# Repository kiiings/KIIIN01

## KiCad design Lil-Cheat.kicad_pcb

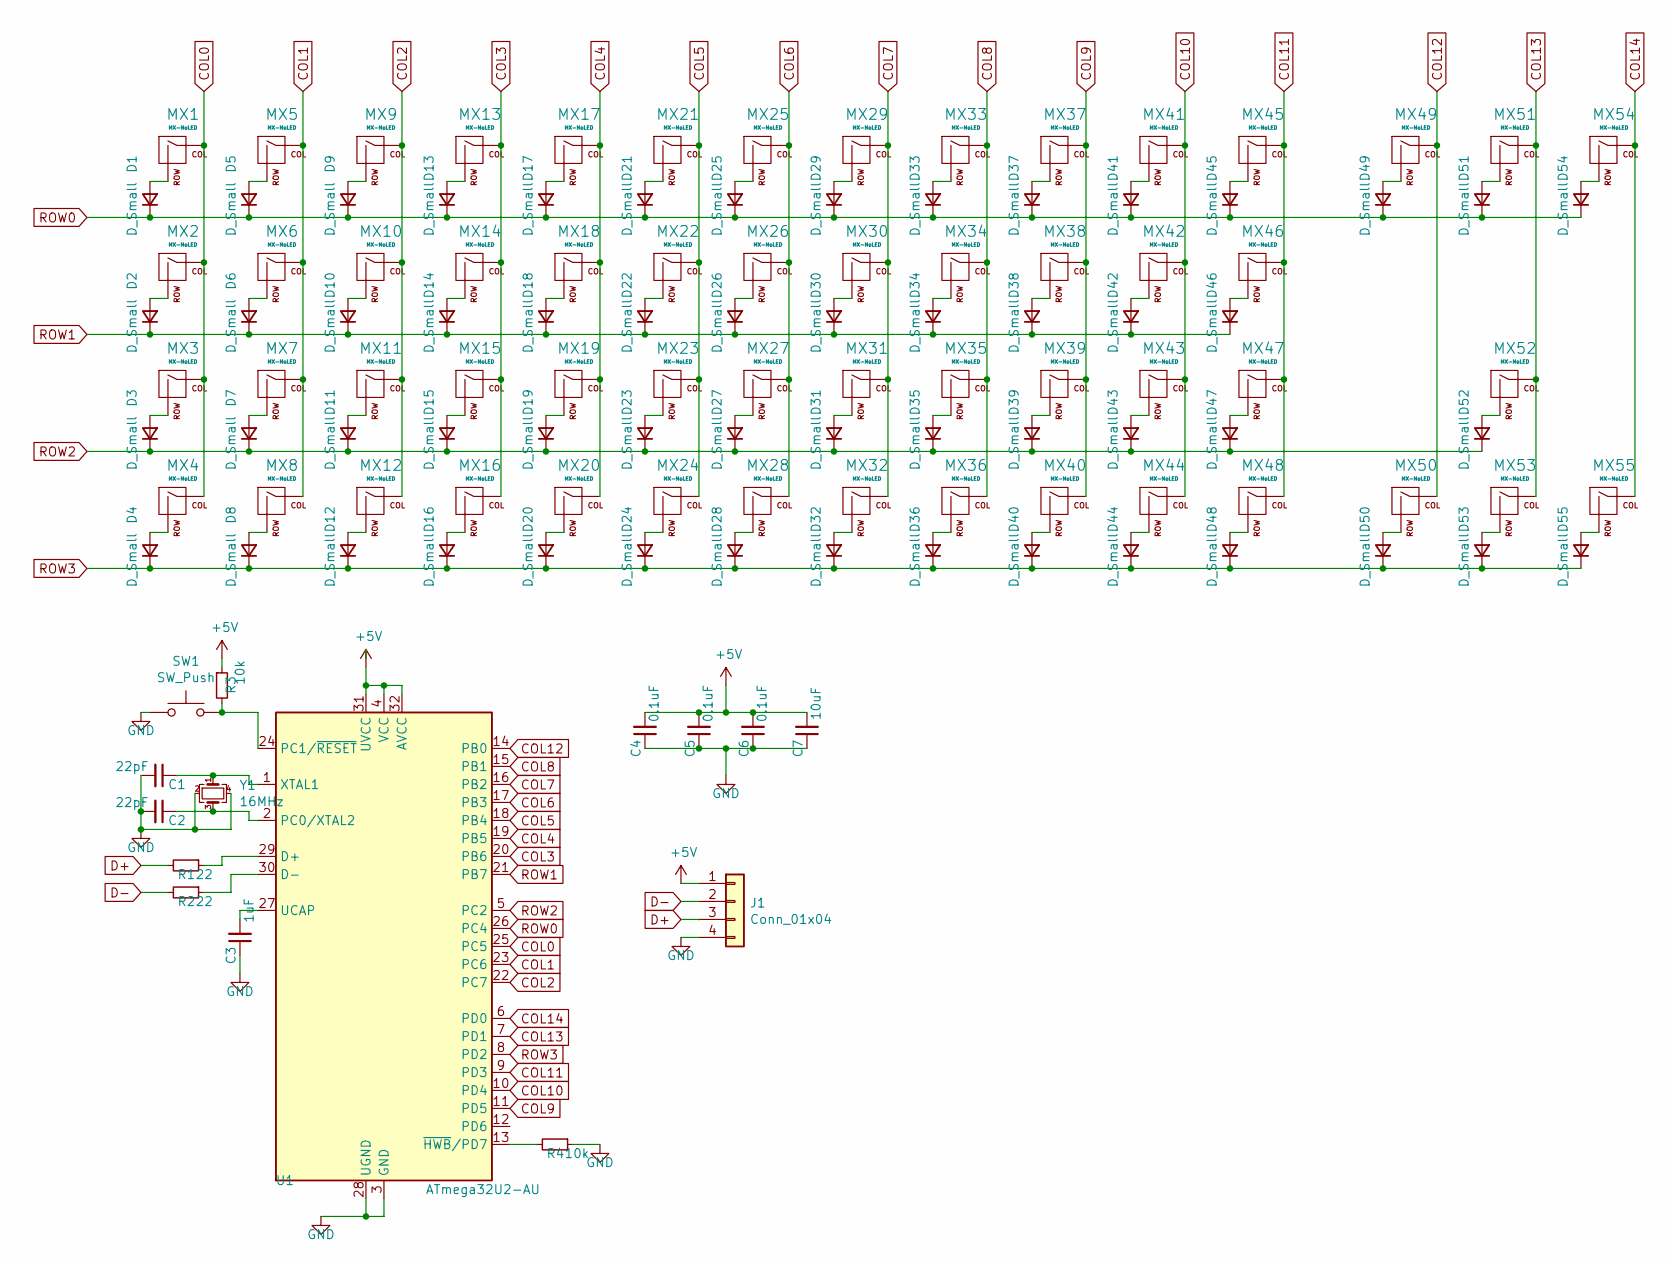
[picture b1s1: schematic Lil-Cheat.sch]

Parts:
C1, C2: 22pF; C_0805_2012Metric
C3: 1uF; C_0805_2012Metric
C4, C5, C6: 0.1uF; C_0805_2012Metric
C7: 10uF; C_0805_2012Metric
D1, D2, D3, D4, D5, D6, D7, D8, D9, D10, D11, D12, D13, D14, D15, D16, D17, D18, D19, D20, D21, D22, D23, D24, D25, D26, D27, D28, D29, D30, D31, D32, D33, D34, D35, D36, D37, D38, D39, D40, D41, D42, D43, D44, D45, D46, D47, D48, D49, D50, D51, D52, D53, D54, D55: D_Small; D_SOD-123
J1: Conn_01x04; JST_SUR_SM04B-SURS-TF_1x04-1MP_P0.80mm_Horizontal
MX1, MX2, MX3, MX4, MX5, MX6, MX7, MX8, MX9, MX10, MX11, MX12, MX13, MX14, MX15, MX16, MX17, MX18, MX19, MX20, MX21, MX22, MX23, MX24, MX25, MX26, MX27, MX28, MX29, MX30, MX31, MX32, MX33, MX34, MX35, MX36, MX37, MX38, MX39, MX40, MX41, MX42, MX43, MX44, MX45, MX46, MX47, MX48, MX49, MX50, MX51, MX52, MX53, MX54, MX55: MX-NoLED; MX-1U
R1, R2: 22; R_0805_2012Metric
R3, R4: 10k; R_0805_2012Metric
SW1: SW_Push; SKQG-1155865
U1: ATmega32U2-AU; TQFP-44_10x10mm_P0.8mm
Y1: 16MHz; Crystal_SMD_3225-4pin_3.2x2.5mm

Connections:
+5V: C4.2, C5.2, C6.2, C7.2, J1.1, R3.1, U1.4 (VCC), U1.31 (UVCC), U1.32 (AVCC)
COL0: MX1.1 (COL), MX2.1 (COL), MX3.1 (COL), MX4.1 (COL), U1.25 (PC5)
COL1: MX5.1 (COL), MX6.1 (COL), MX7.1 (COL), MX8.1 (COL), U1.23 (PC6)
COL2: MX9.1 (COL), MX10.1 (COL), MX11.1 (COL), MX12.1 (COL), U1.22 (PC7)
COL3: MX13.1 (COL), MX14.1 (COL), MX15.1 (COL), MX16.1 (COL), U1.20 (PB6)
COL4: MX17.1 (COL), MX18.1 (COL), MX19.1 (COL), MX20.1 (COL), U1.19 (PB5)
COL5: MX21.1 (COL), MX22.1 (COL), MX23.1 (COL), MX24.1 (COL), U1.18 (PB4)
COL6: MX25.1 (COL), MX26.1 (COL), MX27.1 (COL), MX28.1 (COL), U1.17 (PB3)
COL7: MX29.1 (COL), MX30.1 (COL), MX31.1 (COL), MX32.1 (COL), U1.16 (PB2)
COL8: MX33.1 (COL), MX34.1 (COL), MX35.1 (COL), MX36.1 (COL), U1.15 (PB1)
COL9: MX37.1 (COL), MX38.1 (COL), MX39.1 (COL), MX40.1 (COL), U1.11 (PD5)
COL10: MX41.1 (COL), MX42.1 (COL), MX43.1 (COL), MX44.1 (COL), U1.10 (PD4)
COL11: MX45.1 (COL), MX46.1 (COL), MX47.1 (COL), MX48.1 (COL), U1.9 (PD3)
COL12: MX49.1 (COL), MX50.1 (COL), U1.14 (PB0)
COL13: MX51.1 (COL), MX52.1 (COL), MX53.1 (COL), U1.7 (PD1)
COL14: MX54.1 (COL), MX55.1 (COL), U1.6 (PD0)
D+: J1.3, R1.2
D-: J1.2, R2.2
GND: C1.2, C2.2, C3.1, C4.1, C5.1, C6.1, C7.1, J1.4, R4.1, SW1.1, U1.3 (GND), U1.28 (UGND), Y1.2, Y1.4
unnamed: C1.1, U1.1 (XTAL1), Y1.1
unnamed: C2.1, U1.2 (PC0/XTAL2), Y1.3
unnamed: C3.2, U1.27 (UCAP)
unnamed: D1.2 (A), MX1.2 (ROW)
unnamed: D2.2 (A), MX2.2 (ROW)
unnamed: D3.2 (A), MX3.2 (ROW)
unnamed: D4.2 (A), MX4.2 (ROW)
unnamed: D5.2 (A), MX5.2 (ROW)
unnamed: D6.2 (A), MX6.2 (ROW)
unnamed: D7.2 (A), MX7.2 (ROW)
unnamed: D8.2 (A), MX8.2 (ROW)
unnamed: D9.2 (A), MX9.2 (ROW)
unnamed: D10.2 (A), MX10.2 (ROW)
unnamed: D11.2 (A), MX11.2 (ROW)
unnamed: D12.2 (A), MX12.2 (ROW)
unnamed: D13.2 (A), MX13.2 (ROW)
unnamed: D14.2 (A), MX14.2 (ROW)
unnamed: D15.2 (A), MX15.2 (ROW)
unnamed: D16.2 (A), MX16.2 (ROW)
unnamed: D17.2 (A), MX17.2 (ROW)
unnamed: D18.2 (A), MX18.2 (ROW)
unnamed: D19.2 (A), MX19.2 (ROW)
unnamed: D20.2 (A), MX20.2 (ROW)
unnamed: D21.2 (A), MX21.2 (ROW)
unnamed: D22.2 (A), MX22.2 (ROW)
unnamed: D23.2 (A), MX23.2 (ROW)
unnamed: D24.2 (A), MX24.2 (ROW)
unnamed: D25.2 (A), MX25.2 (ROW)
unnamed: D26.2 (A), MX26.2 (ROW)
unnamed: D27.2 (A), MX27.2 (ROW)
unnamed: D28.2 (A), MX28.2 (ROW)
unnamed: D29.2 (A), MX29.2 (ROW)
unnamed: D30.2 (A), MX30.2 (ROW)
unnamed: D31.2 (A), MX31.2 (ROW)
unnamed: D32.2 (A), MX32.2 (ROW)
unnamed: D33.2 (A), MX33.2 (ROW)
unnamed: D34.2 (A), MX34.2 (ROW)
unnamed: D35.2 (A), MX35.2 (ROW)
unnamed: D36.2 (A), MX36.2 (ROW)
unnamed: D37.2 (A), MX37.2 (ROW)
unnamed: D38.2 (A), MX38.2 (ROW)
unnamed: D39.2 (A), MX39.2 (ROW)
unnamed: D40.2 (A), MX40.2 (ROW)
unnamed: D41.2 (A), MX41.2 (ROW)
unnamed: D42.2 (A), MX42.2 (ROW)
unnamed: D43.2 (A), MX43.2 (ROW)
unnamed: D44.2 (A), MX44.2 (ROW)
unnamed: D45.2 (A), MX45.2 (ROW)
unnamed: D46.2 (A), MX46.2 (ROW)
unnamed: D47.2 (A), MX47.2 (ROW)
unnamed: D48.2 (A), MX48.2 (ROW)
unnamed: D49.2 (A), MX49.2 (ROW)
unnamed: D50.2 (A), MX50.2 (ROW)
unnamed: D51.2 (A), MX51.2 (ROW)
unnamed: D52.2 (A), MX52.2 (ROW)
unnamed: D53.2 (A), MX53.2 (ROW)
unnamed: D54.2 (A), MX54.2 (ROW)
unnamed: D55.2 (A), MX55.2 (ROW)
unnamed: R1.1, U1.29 (D+)
unnamed: R2.1, U1.30 (D-)
unnamed: R3.2, SW1.2, U1.24 (PC1/~RESET)
unnamed: R4.2, U1.13 (~HWB~/PD7)
ROW0: D1.1 (K), D5.1 (K), D9.1 (K), D13.1 (K), D17.1 (K), D21.1 (K), D25.1 (K), D29.1 (K), D33.1 (K), D37.1 (K), D41.1 (K), D45.1 (K), D49.1 (K), D51.1 (K), D54.1 (K), U1.26 (PC4)
ROW1: D2.1 (K), D6.1 (K), D10.1 (K), D14.1 (K), D18.1 (K), D22.1 (K), D26.1 (K), D30.1 (K), D34.1 (K), D38.1 (K), D42.1 (K), D46.1 (K), U1.21 (PB7)
ROW2: D3.1 (K), D7.1 (K), D11.1 (K), D15.1 (K), D19.1 (K), D23.1 (K), D27.1 (K), D31.1 (K), D35.1 (K), D39.1 (K), D43.1 (K), D47.1 (K), D52.1 (K), U1.5 (PC2)
ROW3: D4.1 (K), D8.1 (K), D12.1 (K), D16.1 (K), D20.1 (K), D24.1 (K), D28.1 (K), D32.1 (K), D36.1 (K), D40.1 (K), D44.1 (K), D48.1 (K), D50.1 (K), D53.1 (K), D55.1 (K), U1.8 (PD2)

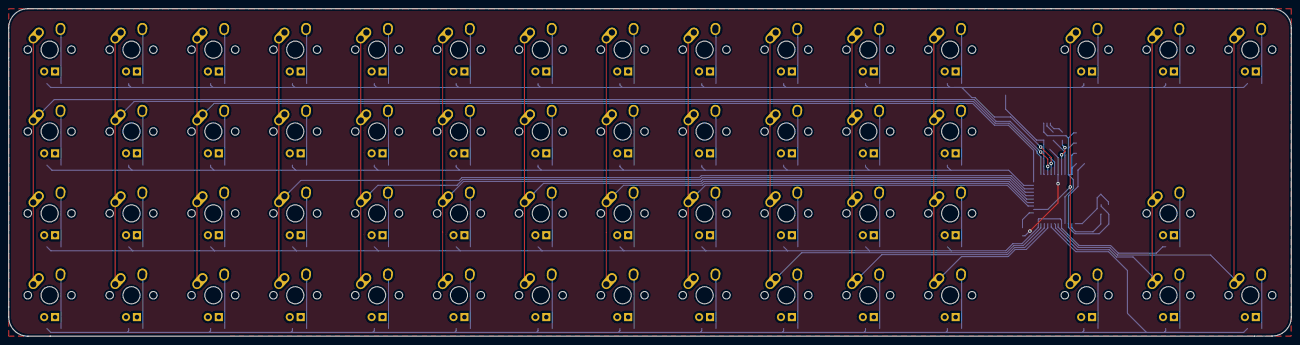
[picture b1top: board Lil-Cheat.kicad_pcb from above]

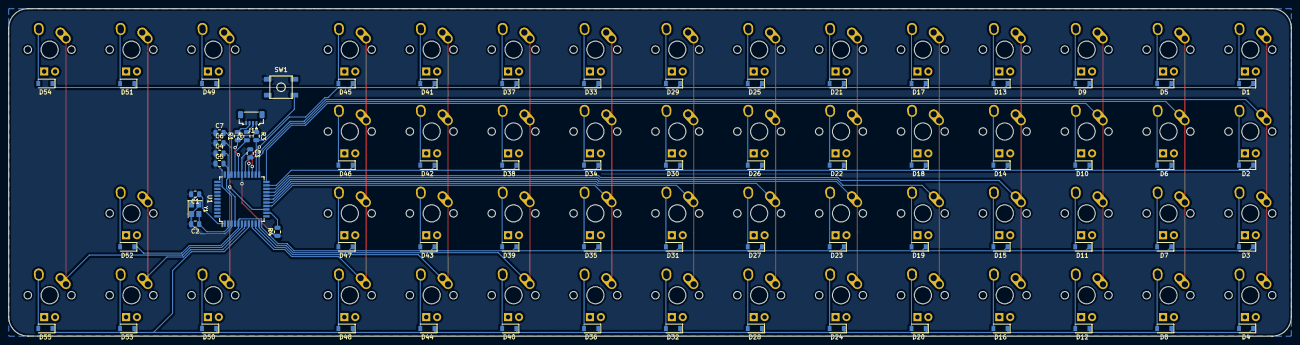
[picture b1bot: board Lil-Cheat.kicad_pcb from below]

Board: 2 copper layers, 298.4 x 76.2 mm, 125 parts (70 on the bottom side), 85 nets.

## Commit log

2020-10-02 initial commit 💀
2020-10-03 swapped to daughterboard
2020-10-13 initial staggered commit
2020-10-13 project tidy
2020-10-29 staggered init
